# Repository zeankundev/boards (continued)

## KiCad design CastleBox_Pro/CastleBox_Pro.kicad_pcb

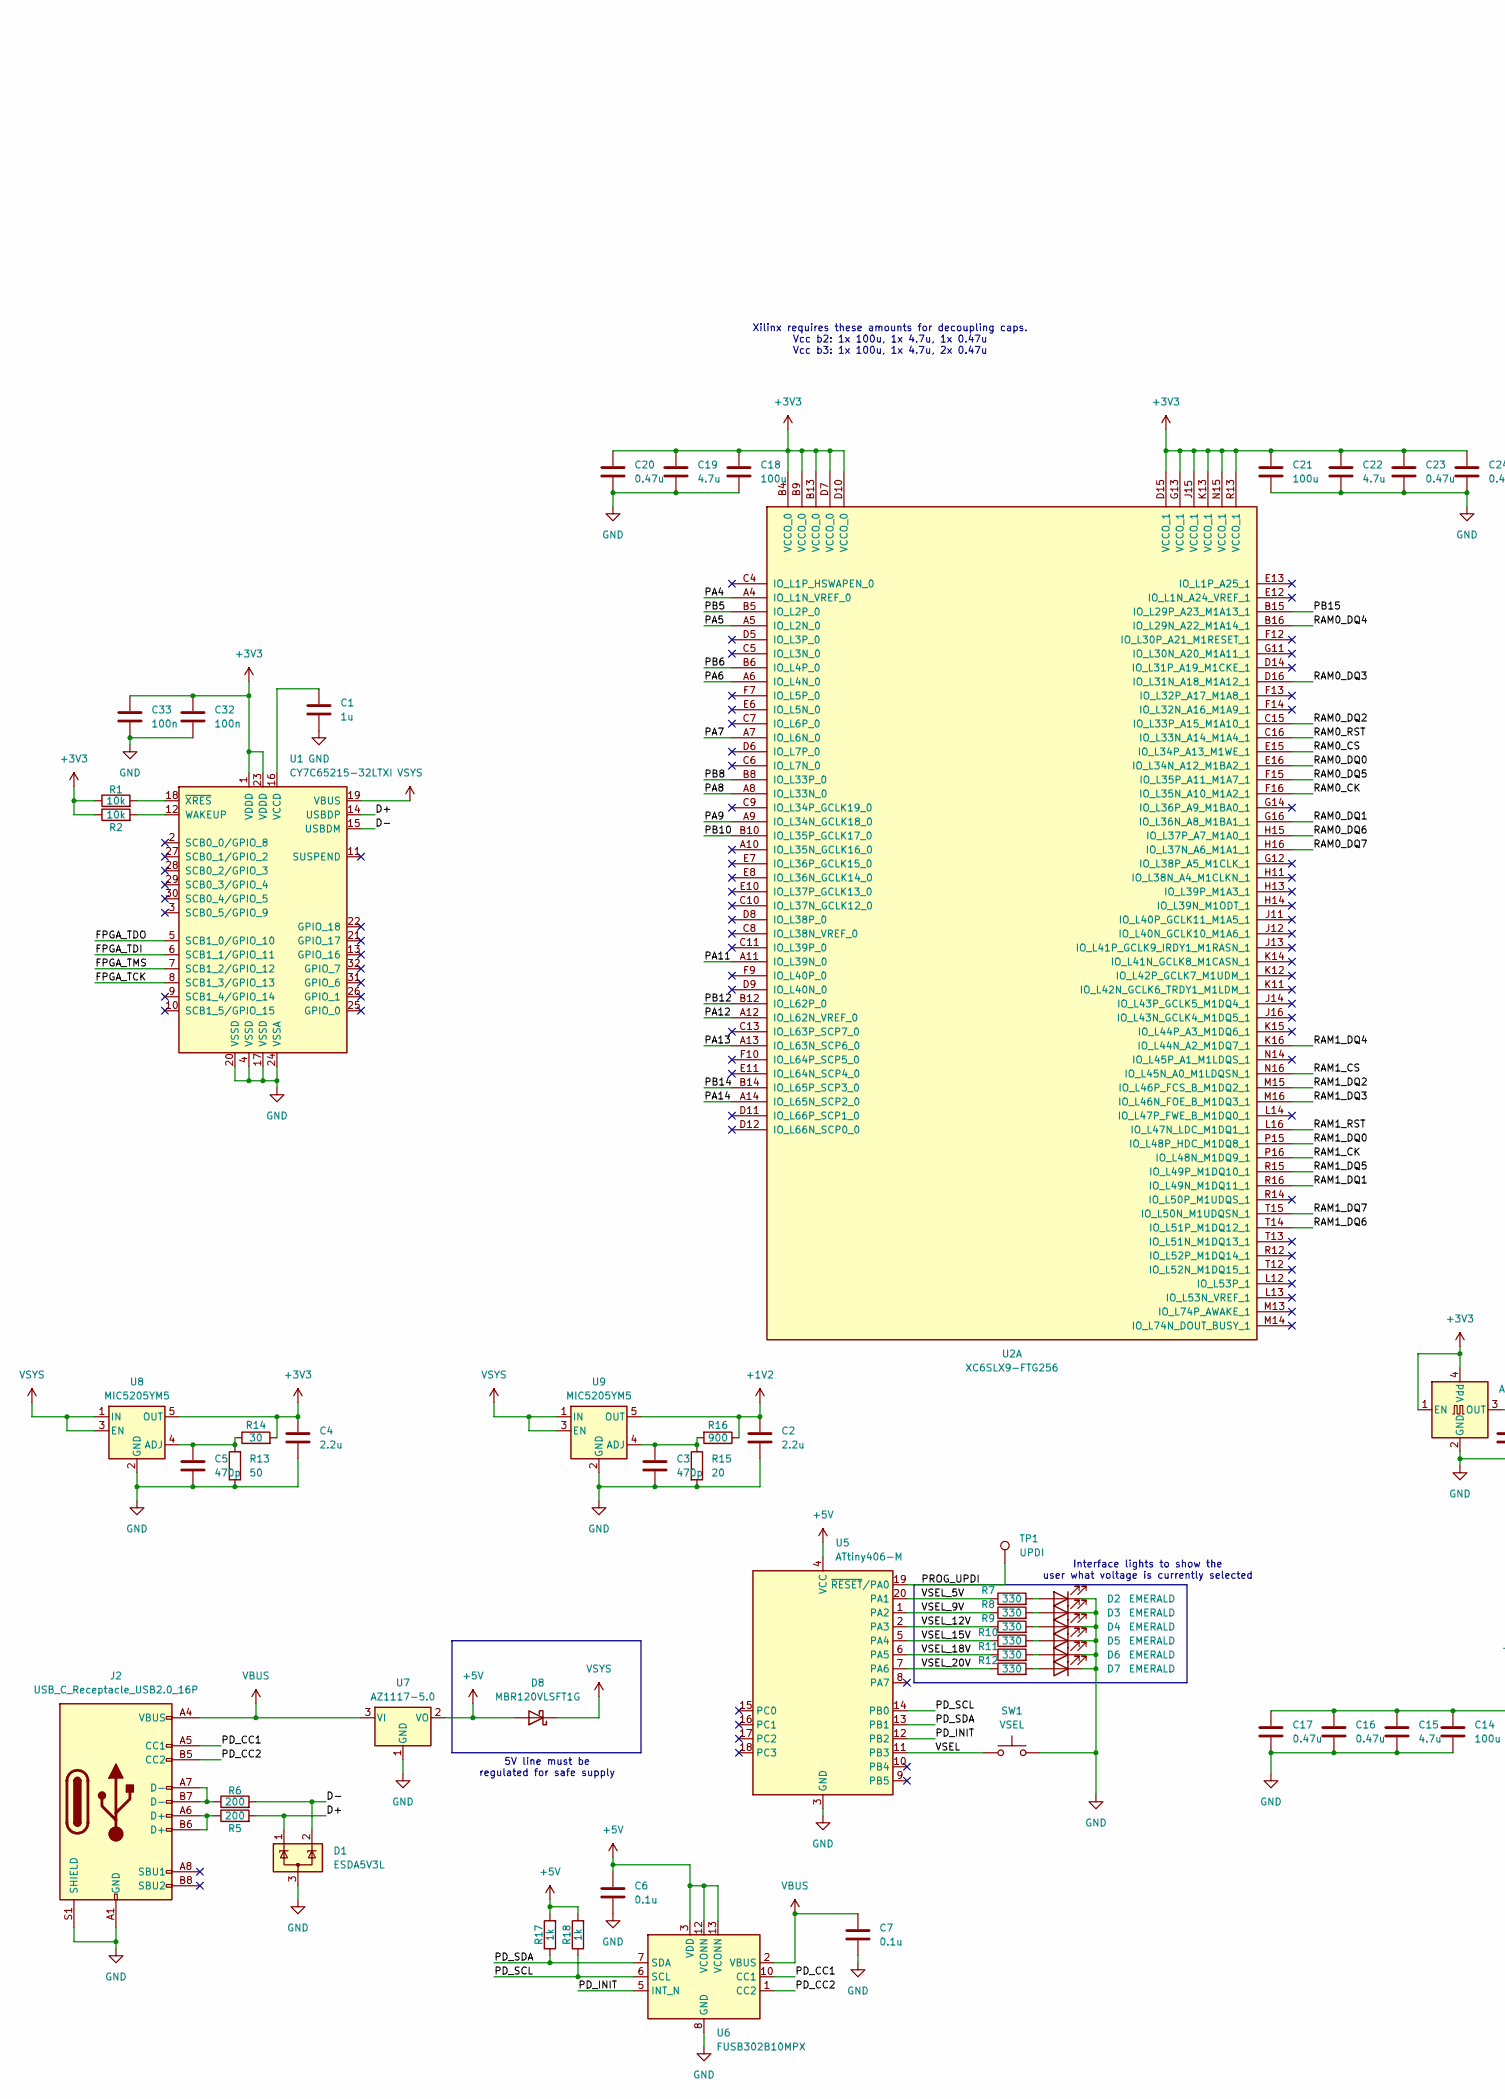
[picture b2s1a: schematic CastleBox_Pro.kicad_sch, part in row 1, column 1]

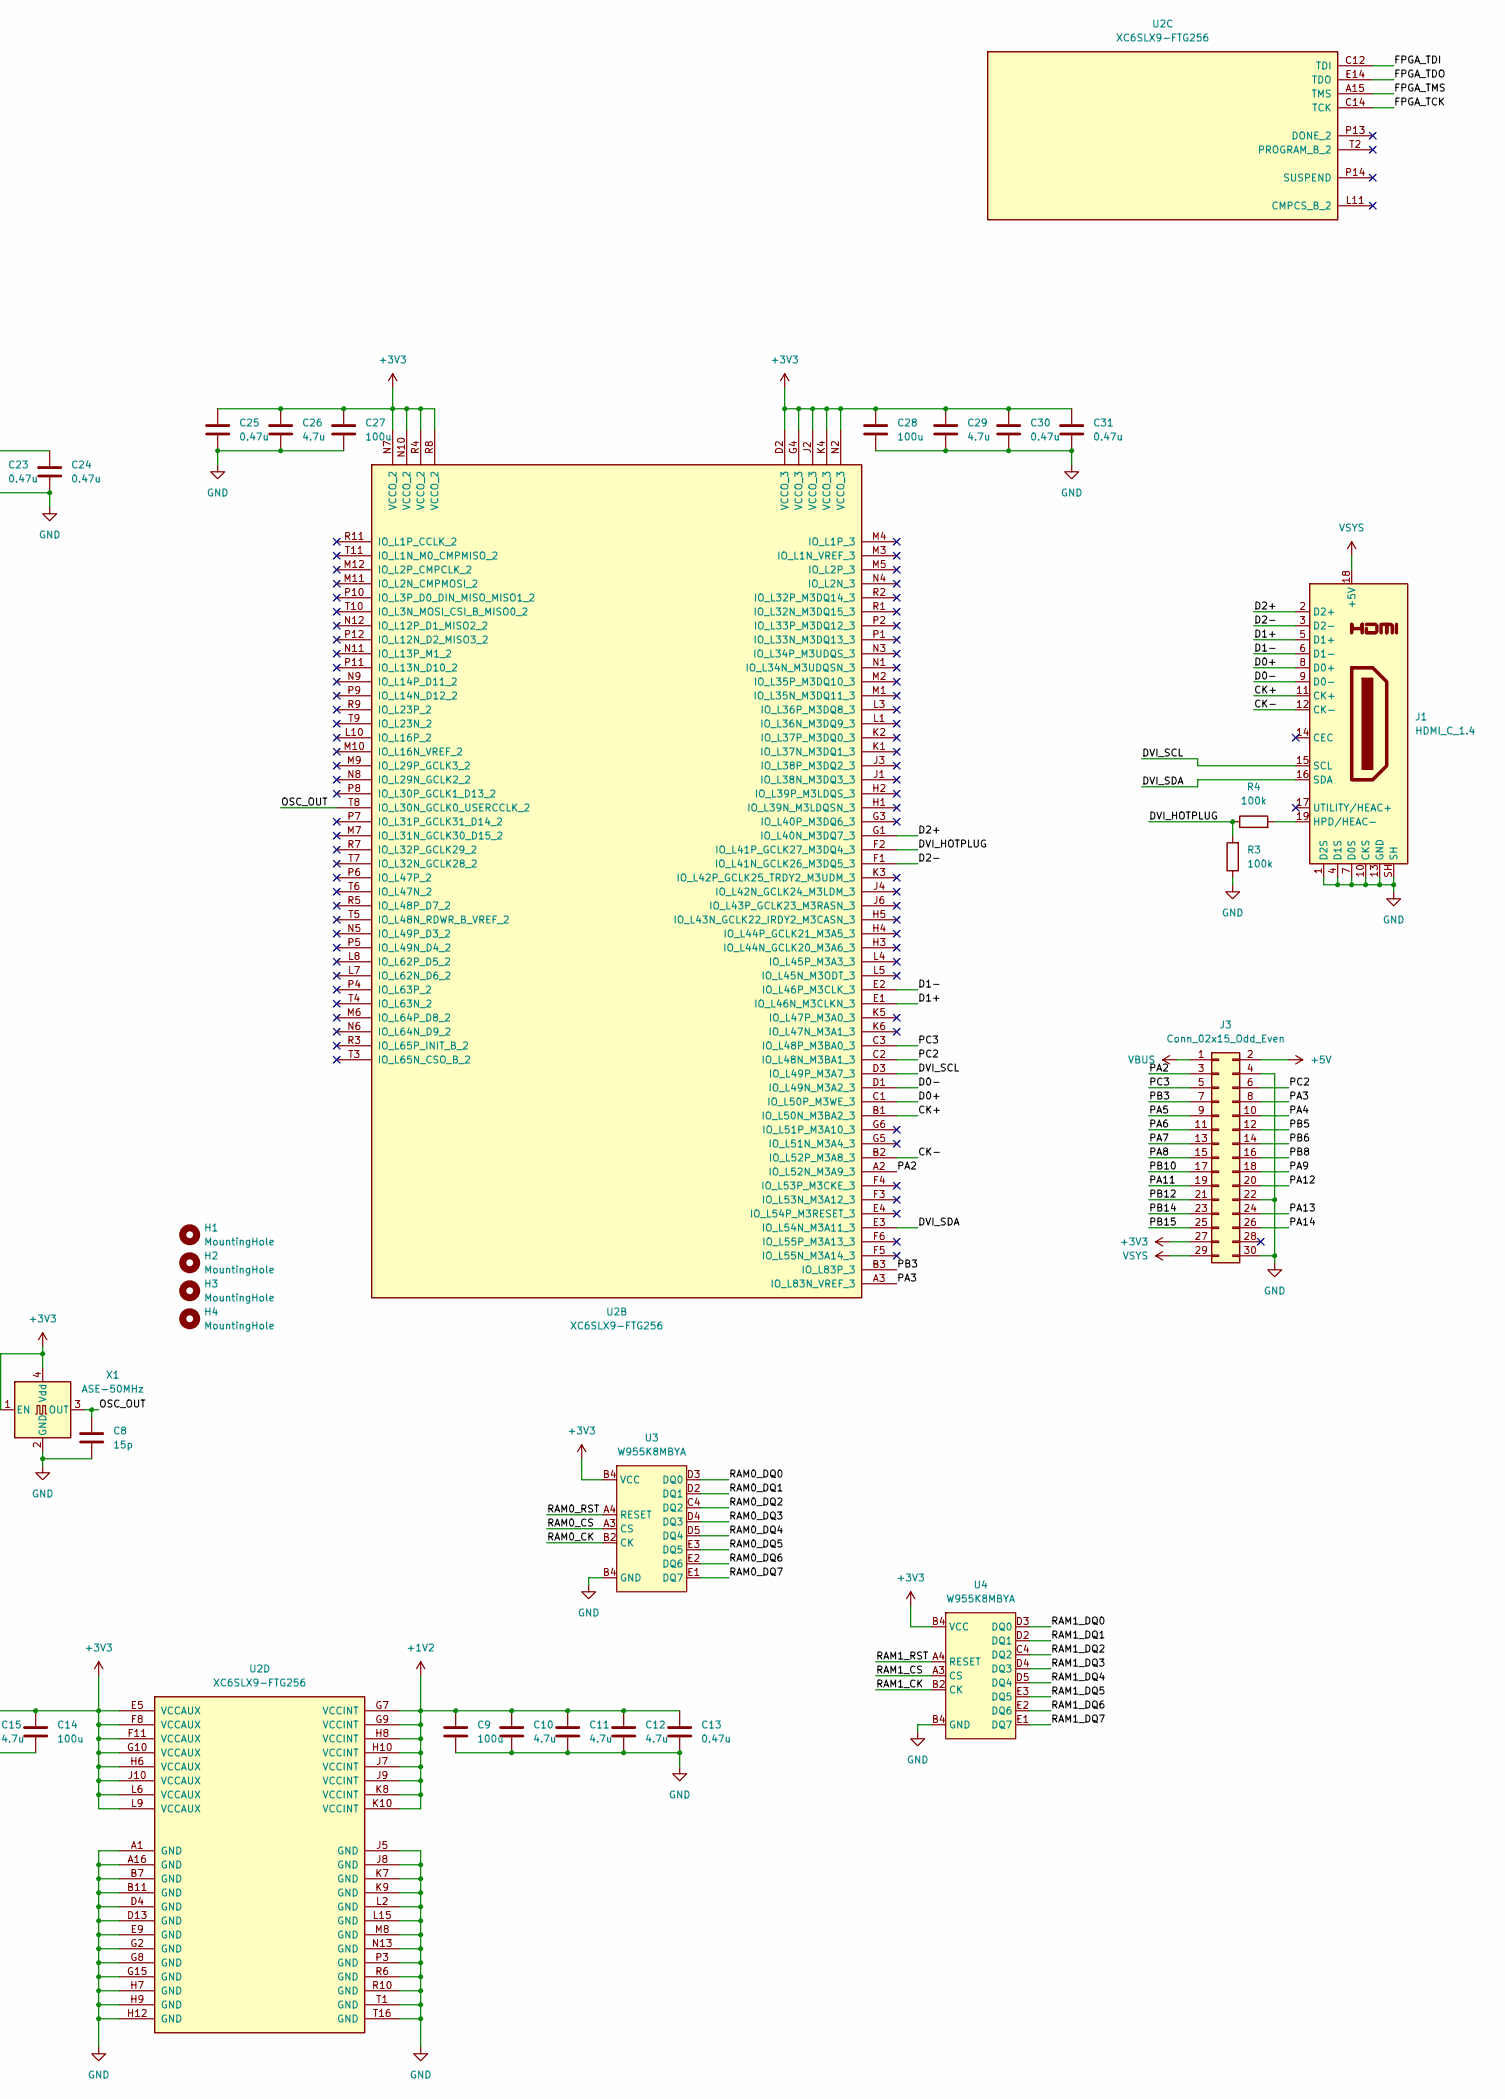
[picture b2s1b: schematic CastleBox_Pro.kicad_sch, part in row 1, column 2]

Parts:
C1: 1u; C_0402_1005Metric
C2, C4: 2.2u; C_0402_1005Metric
C3, C5: 470p; C_0402_1005Metric
C6, C7: 0.1u; C_0402_1005Metric
C8: 15p; C_0402_1005Metric
C9, C14, C18, C21, C27, C28: 100u; C_0402_1005Metric
C10, C11, C12, C15, C19, C22, C26, C29: 4.7u; C_0402_1005Metric
C13, C16, C17, C20, C23, C24, C25, C30, C31: 0.47u; C_0402_1005Metric
C32, C33: 100n; C_0402_1005Metric
D1: ESDA5V3L; SOT-23-3
D2, D3, D4, D5, D6, D7: EMERALD; LED_0402_1005Metric
D8: MBR120VLSFT1G; D_SOD-123F
H1, H2, H3, H4: MountingHole; MountingHole_2.1mm
J1: HDMI_C_1.4; VALCON_HD-RA-DSF12-TR
J2: USB_C_Receptacle_USB2.0_16P; USB_C_Receptacle_GCT_USB4105-xx-A_16P_TopMnt_Horizontal
J3: Conn_02x15_Odd_Even; PinHeader_2x15_P2.54mm_Vertical
R1, R2: 10k; R_0402_1005Metric
R3, R4: 100k; R_0402_1005Metric
R5, R6: 200; R_0402_1005Metric
R7, R8, R9, R10, R11, R12: 330; R_0402_1005Metric
R13: 50; R_0402_1005Metric
R14: 30; R_0402_1005Metric
R15: 20; R_0402_1005Metric
R16: 900; R_0402_1005Metric
R17, R18: 1k; R_0402_1005Metric
SW1: VSEL; SW_Push_1P1T_NO_Vertical_Wuerth_434133025816
TP1: UPDI; TestPoint_Pad_D1.0mm
U1: CY7C65215-32LTXI; QFN-32-1EP_5x5mm_P0.5mm_EP3.45x3.45mm
U2: XC6SLX9-FTG256; BGA-256_17.0x17.0mm_Layout16x16_P1.0mm_Ball0.5mm_Pad0.4mm_N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
U3, U4: W955K8MBYA
U5: ATtiny406-M; VQFN-20-1EP_3x3mm_P0.4mm_EP1.7x1.7mm
U6: FUSB302B10MPX; WQFN-14-1EP_2.5x2.5mm_P0.5mm_EP1.45x1.45mm
U7: AZ1117-5.0; SOT-89-3
U8, U9: MIC5205YM5; SOT-23-5
X1: ASE-50MHz; Oscillator_SMD_Abracon_ASE-4Pin_3.2x2.5mm

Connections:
+1V2: C2.1, C9.1, C10.1, C11.1, C12.1, C13.1, R16.1, U2.G7 (VCCINT), U2.G9 (VCCINT), U2.H8 (VCCINT), U2.H10 (VCCINT), U2.J7 (VCCINT), U2.J9 (VCCINT), U2.K8 (VCCINT), U2.K10 (VCCINT), U9.5 (OUT)
+5V: C6.1, D8.2 (A), J3.2, R17.2, R18.2, U5.4 (VCC), U6.3 (VDD), U6.4 (VDD), U6.12 (VCONN), U6.13 (VCONN), U7.2 (VO)
/CK+: J1.11 (CK+), U2.B1 (IO_L50N_M3BA2_3)
/CK-: J1.12 (CK-), U2.B2 (IO_L52P_M3A8_3)
/D0+: J1.8 (D0+), U2.C1 (IO_L50P_M3WE_3)
/D0-: J1.9 (D0-), U2.D1 (IO_L49N_M3A2_3)
/D1+: J1.5 (D1+), U2.E1 (IO_L46N_M3CLKN_3)
/D1-: J1.6 (D1-), U2.E2 (IO_L46P_M3CLK_3)
/D2+: J1.2 (D2+), U2.G1 (IO_L40N_M3DQ7_3)
/D2-: J1.3 (D2-), U2.F1 (IO_L41N_GCLK26_M3DQ5_3)
/D+: D1.1 (K), R5.2, U1.14 (USBDP)
/D-: D1.2 (K), R6.2, U1.15 (USBDM)
/DVI_HOTPLUG: R3.2, R4.1, U2.F2 (IO_L41P_GCLK27_M3DQ4_3)
/DVI_SCL: J1.15 (SCL), U2.D3 (IO_L49P_M3A7_3)
/DVI_SDA: J1.16 (SDA), U2.E3 (IO_L54N_M3A11_3)
/FPGA_TCK: U1.8 (SCB1_3/GPIO_13), U2.C14 (TCK)
/FPGA_TDI: U1.6 (SCB1_1/GPIO_11), U2.C12 (TDI)
/FPGA_TDO: U1.5 (SCB1_0/GPIO_10), U2.E14 (TDO)
/FPGA_TMS: U1.7 (SCB1_2/GPIO_12), U2.A15 (TMS)
/OSC_OUT: C8.1, U2.T8 (IO_L30N_GCLK0_USERCCLK_2), X1.3 (OUT)
/PA2: J3.3, U2.A2 (IO_L52N_M3A9_3)
/PA3: J3.8, U2.A3 (IO_L83N_VREF_3)
/PA4: J3.10, U2.A4 (IO_L1N_VREF_0)
/PA5: J3.9, U2.A5 (IO_L2N_0)
/PA6: J3.11, U2.A6 (IO_L4N_0)
/PA7: J3.13, U2.A7 (IO_L6N_0)
/PA8: J3.15, U2.A8 (IO_L33N_0)
/PA9: J3.18, U2.A9 (IO_L34N_GCLK18_0)
/PA11: J3.19, U2.A11 (IO_L39N_0)
/PA12: J3.20, U2.A12 (IO_L62N_VREF_0)
/PA13: J3.24, U2.A13 (IO_L63N_SCP6_0)
/PA14: J3.26, U2.A14 (IO_L65N_SCP2_0)
/PB3: J3.7, U2.B3 (IO_L83P_3)
/PB5: J3.12, U2.B5 (IO_L2P_0)
/PB6: J3.14, U2.B6 (IO_L4P_0)
/PB8: J3.16, U2.B8 (IO_L33P_0)
/PB10: J3.17, U2.B10 (IO_L35P_GCLK17_0)
/PB12: J3.21, U2.B12 (IO_L62P_0)
/PB14: J3.23, U2.B14 (IO_L65P_SCP3_0)
/PB15: J3.25, U2.B15 (IO_L29P_A23_M1A13_1)
/PC2: J3.6, U2.C2 (IO_L48N_M3BA1_3)
/PC3: J3.5, U2.C3 (IO_L48P_M3BA0_3)
/PD_CC1: J2.A5 (CC1), U6.10 (CC1), U6.11 (CC1)
/PD_CC2: J2.B5 (CC2), U6.1 (CC2), U6.14 (CC2)
/PD_INIT: U5.12 (PB2), U6.5 (INT_N)
/PD_SCL: R18.1, U5.14 (PB0), U6.6 (SCL)
/PD_SDA: R17.1, U5.13 (PB1), U6.7 (SDA)
/PROG_UPDI: TP1.1, U5.19 (~RESET/PA0)
/RAM0_CK: U2.F16 (IO_L35N_A10_M1A2_1), U3.B2 (CK)
/RAM0_CS: U2.E15 (IO_L34P_A13_M1WE_1), U3.A3 (CS)
/RAM0_DQ0: U2.E16 (IO_L34N_A12_M1BA2_1), U3.D3 (DQ0)
/RAM0_DQ1: U2.G16 (IO_L36N_A8_M1BA1_1), U3.D2 (DQ1)
/RAM0_DQ2: U2.C15 (IO_L33P_A15_M1A10_1), U3.C4 (DQ2)
/RAM0_DQ3: U2.D16 (IO_L31N_A18_M1A12_1), U3.D4 (DQ3)
/RAM0_DQ4: U2.B16 (IO_L29N_A22_M1A14_1), U3.D5 (DQ4)
/RAM0_DQ5: U2.F15 (IO_L35P_A11_M1A7_1), U3.E3 (DQ5)
/RAM0_DQ6: U2.H15 (IO_L37P_A7_M1A0_1), U3.E2 (DQ6)
/RAM0_DQ7: U2.H16 (IO_L37N_A6_M1A1_1), U3.E1 (DQ7)
/RAM0_RST: U2.C16 (IO_L33N_A14_M1A4_1), U3.A4 (RESET)
/RAM1_CK: U2.P16 (IO_L48N_M1DQ9_1), U4.B2 (CK)
/RAM1_CS: U2.N16 (IO_L45N_A0_M1LDQSN_1), U4.A3 (CS)
/RAM1_DQ0: U2.P15 (IO_L48P_HDC_M1DQ8_1), U4.D3 (DQ0)
/RAM1_DQ1: U2.R16 (IO_L49N_M1DQ11_1), U4.D2 (DQ1)
/RAM1_DQ2: U2.M15 (IO_L46P_FCS_B_M1DQ2_1), U4.C4 (DQ2)
/RAM1_DQ3: U2.M16 (IO_L46N_FOE_B_M1DQ3_1), U4.D4 (DQ3)
/RAM1_DQ4: U2.K16 (IO_L44N_A2_M1DQ7_1), U4.D5 (DQ4)
/RAM1_DQ5: U2.R15 (IO_L49P_M1DQ10_1), U4.E3 (DQ5)
/RAM1_DQ6: U2.T14 (IO_L51P_M1DQ12_1), U4.E2 (DQ6)
/RAM1_DQ7: U2.T15 (IO_L50N_M1UDQSN_1), U4.E1 (DQ7)
/RAM1_RST: U2.L16 (IO_L47N_LDC_M1DQ1_1), U4.A4 (RESET)
/VSEL: SW1.1, U5.11 (PB3)
/VSEL_5V: R7.1, U5.20 (PA1)
/VSEL_9V: R8.1, U5.1 (PA2)
/VSEL_12V: R9.1, U5.2 (PA3)
/VSEL_15V: R10.1, U5.5 (PA4)
/VSEL_18V: R11.1, U5.6 (PA5)
/VSEL_20V: R12.1, U5.7 (PA6)
unnamed: D2.2 (A), R7.2
unnamed: D3.2 (A), R8.2
unnamed: D4.2 (A), R9.2
unnamed: D5.2 (A), R10.2
unnamed: D6.2 (A), R11.2
unnamed: D7.2 (A), R12.2
unnamed: J1.19 (HPD/HEAC-), R4.2
unnamed: J2.A6 (D+), J2.B6 (D+), R5.1
unnamed: J2.A7 (D-), J2.B7 (D-), R6.1
unnamed: C1.1, U1.16 (VCCD)
unnamed: R2.2, U1.12 (WAKEUP)
unnamed: R1.2, U1.18 (~XRES)
unnamed: C5.1, R13.2, R14.1, U8.4 (ADJ)
unnamed: C3.1, R15.1, R16.2, U9.4 (ADJ)
VBUS: C7.1, J2.A4 (VBUS), J2.A9 (VBUS), J2.B4 (VBUS), J2.B9 (VBUS), J3.1, U6.2 (VBUS), U7.3 (VI)
VSYS: D8.1 (K), J1.18 (+5V), J3.29, U1.19 (VBUS), U8.1 (IN), U8.3 (EN), U9.1 (IN), U9.3 (EN)

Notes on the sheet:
5V line must be regulated for safe supply
Xilinx requires these amounts for decoupling caps. Vcc b2: 1x 100u, 1x 4.7u, 1x 0.47u Vcc b3: 1x 100u, 1x 4.7u, 2x 0.47u
Interface lights to show the user what voltage is currently selected

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
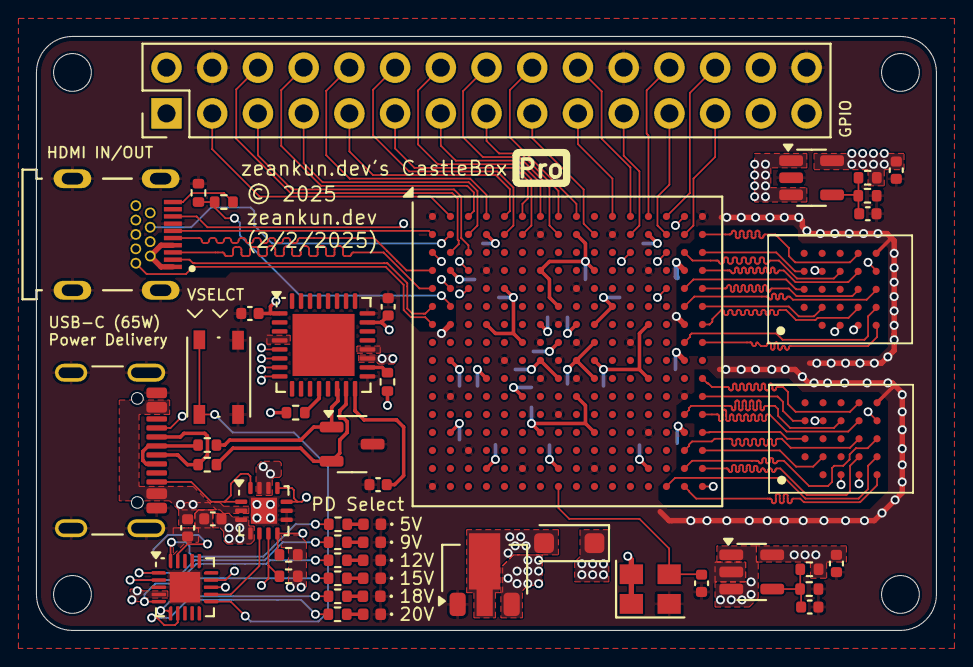
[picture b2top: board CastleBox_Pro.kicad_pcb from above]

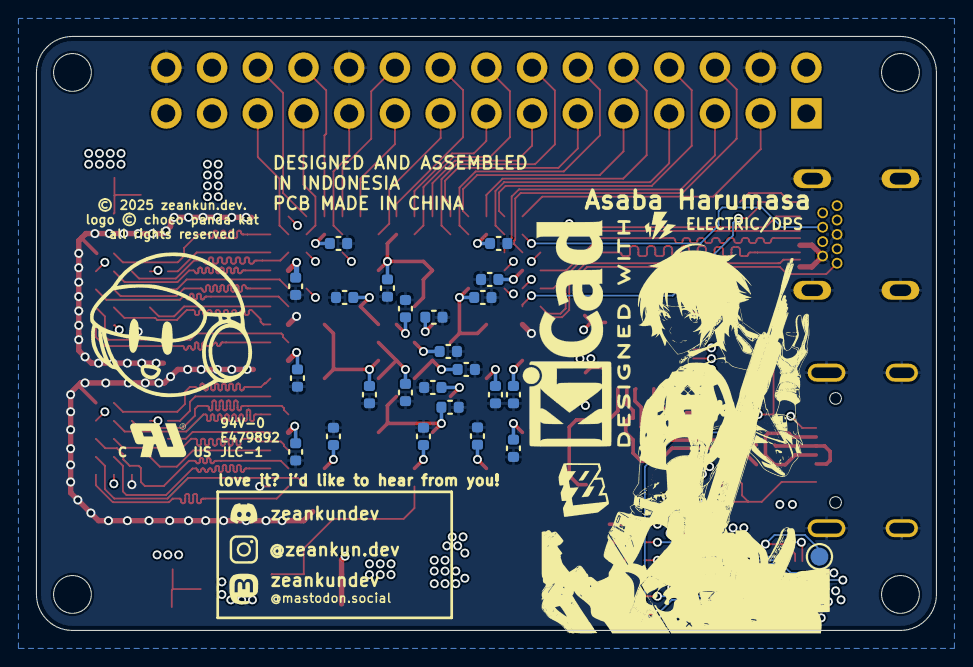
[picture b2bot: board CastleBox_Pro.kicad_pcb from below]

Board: 6 copper layers, 50.0 x 33.0 mm, 78 parts (24 on the bottom side), 95 nets.

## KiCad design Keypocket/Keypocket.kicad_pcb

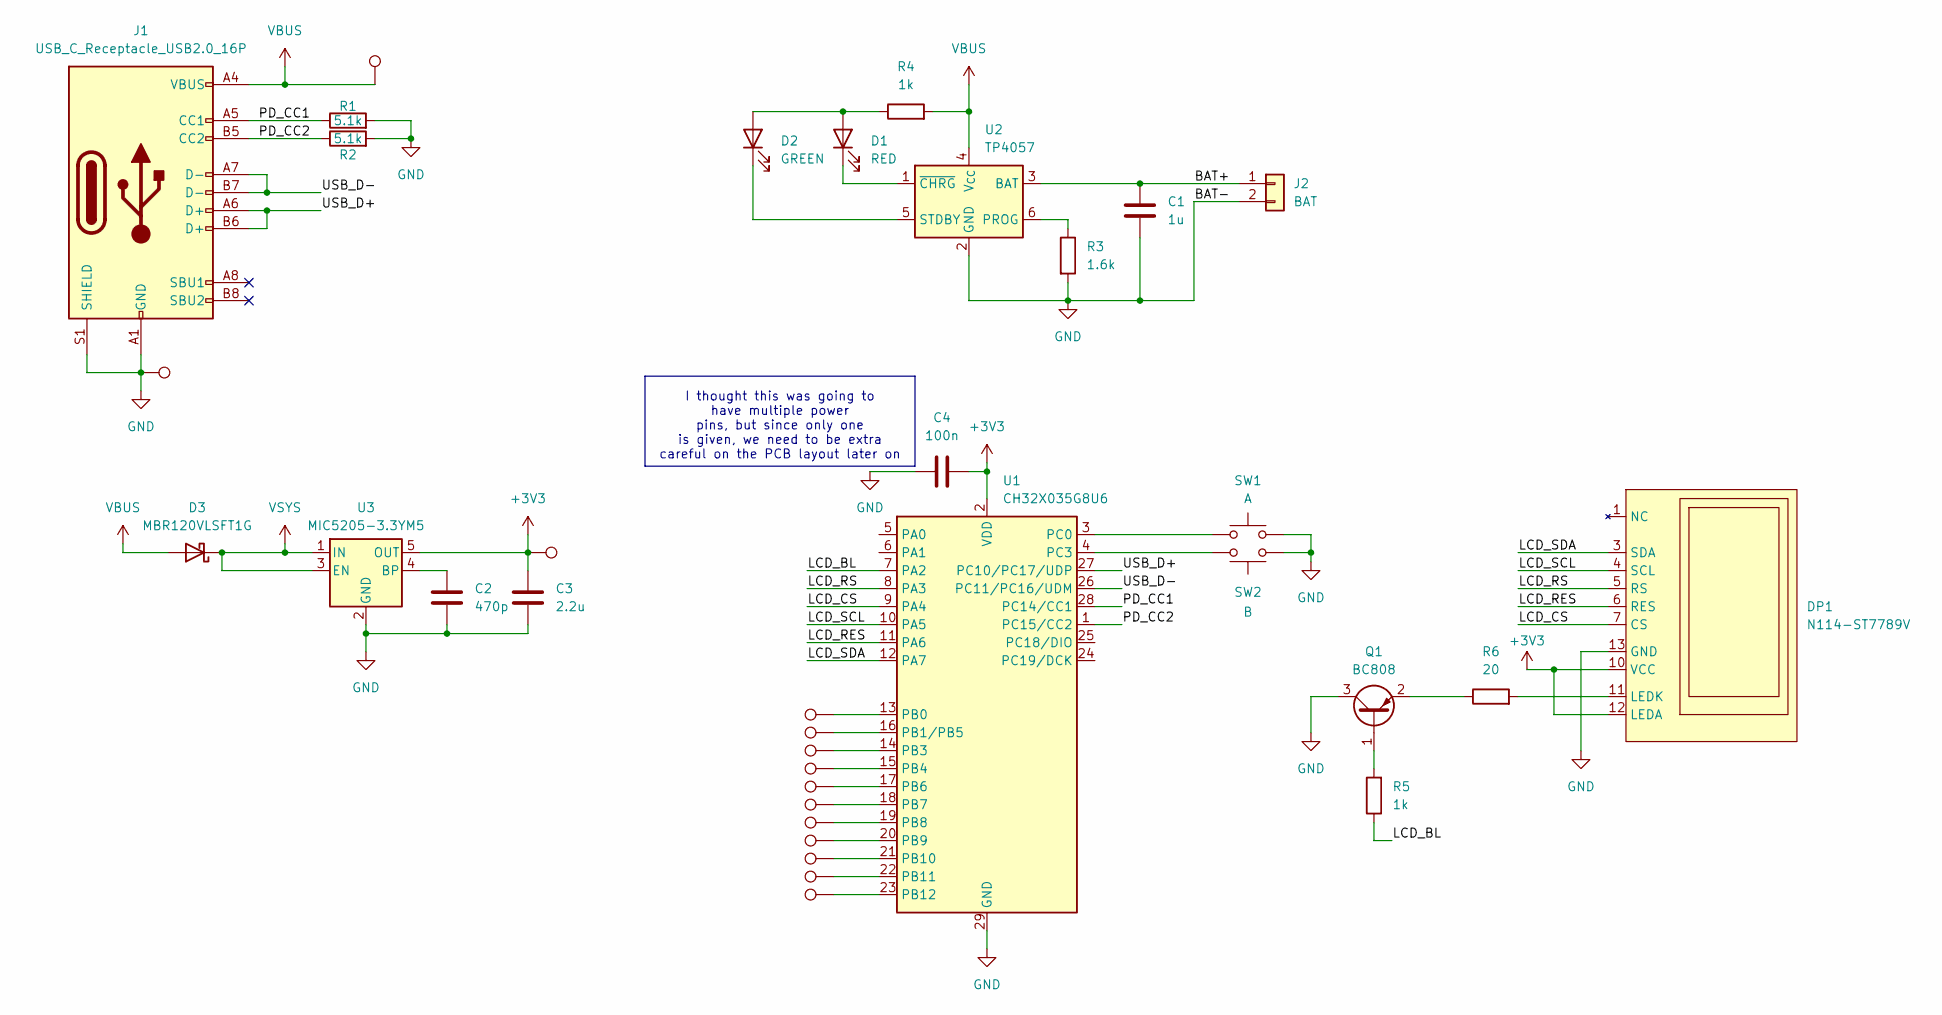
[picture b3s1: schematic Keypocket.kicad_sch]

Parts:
C1: 1u; C_0603_1608Metric
C2: 470p; C_0402_1005Metric
C3: 2.2u; C_0603_1608Metric
C4: 100n; C_0402_1005Metric
D1: RED; LED_0402_1005Metric
D2: GREEN; LED_0402_1005Metric
D3: MBR120VLSFT1G; D_SOD-123F
DP1: N114-ST7789V; ST7789-114
J1: USB_C_Receptacle_USB2.0_16P; USB_C_Receptacle_GCT_USB4110
J2: BAT; SolderWire-0.1sqmm_1x02_P3.6mm_D0.4mm_OD1mm
Q1: BC808; SOT-23
R1, R2: 5.1k; R_0402_1005Metric
R3: 1.6k; R_0402_1005Metric
R4, R5: 1k; R_0402_1005Metric
R6: 20; R_0402_1005Metric
SW1: A; SW_Push_1P1T_NO_Vertical_Wuerth_434133025816
SW2: B; SW_Push_1P1T_NO_Vertical_Wuerth_434133025816
TP1, TP2, TP3, TP4, TP5, TP6, TP7, TP8, TP9, TP10, TP11: TestPoint; TestPoint_Keystone_5015_Micro_Mini
TP12, TP13, TP14: TestPoint; TestPoint_Pad_2.0x2.0mm
U1: CH32X035G8U6; QFN-28-1EP_4x4mm_P0.4mm_EP2.7x2.7mm
U2: TP4057; TSOT-23-6
U3: MIC5205-3.3YM5; SOT-23-5

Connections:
+3V3: C3.1, C4.2, DP1.10 (VCC), DP1.12 (LEDA), TP12.1, U1.2 (VDD), U3.5 (OUT)
/BAT+: C1.1, J2.1, U2.3 (BAT)
/LCD_BL: R5.1, U1.7 (PA2)
/LCD_CS: DP1.7 (CS), U1.9 (PA4)
/LCD_RES: DP1.6 (RES), U1.11 (PA6)
/LCD_RS: DP1.5 (RS), U1.8 (PA3)
/LCD_SCL: DP1.4 (SCL), U1.10 (PA5)
/LCD_SDA: DP1.3 (SDA), U1.12 (PA7)
/PD_CC1: J1.A5 (CC1), R1.1, U1.28 (PC14/CC1)
/PD_CC2: J1.B5 (CC2), R2.1, U1.1 (PC15/CC2)
/USB_D+: J1.A6 (D+), J1.B6 (D+), U1.27 (PC10/PC17/UDP)
/USB_D-: J1.A7 (D-), J1.B7 (D-), U1.26 (PC11/PC16/UDM)
GND: C1.2, C2.2, C3.2, C4.1, DP1.8 (GND), DP1.13 (GND), J1.A1 (GND), J1.A12 (GND), J1.B1 (GND), J1.B12 (GND), J1.S1 (SHIELD), J2.2, Q1.3 (C), R1.2, R2.2, R3.2, SW1.2, SW2.1, TP14.1, U1.29 (GND), U2.2 (GND), U3.2 (GND)
unnamed: D1.2 (A), D2.2 (A), R4.1
unnamed: D1.1 (K), U2.1 (~CHRG)
unnamed: D2.1 (K), U2.5 (STDBY)
unnamed: DP1.11 (LEDK), R6.2
unnamed: Q1.1 (B), R5.2
unnamed: Q1.2 (E), R6.1
unnamed: TP1.1, U1.13 (PB0)
unnamed: TP2.1, U1.16 (PB1/PB5)
unnamed: TP3.1, U1.14 (PB3)
unnamed: TP4.1, U1.15 (PB4)
unnamed: TP5.1, U1.17 (PB6)
unnamed: TP6.1, U1.18 (PB7)
unnamed: TP7.1, U1.19 (PB8)
unnamed: TP8.1, U1.20 (PB9)
unnamed: TP9.1, U1.21 (PB10)
unnamed: TP10.1, U1.22 (PB11)
unnamed: TP11.1, U1.23 (PB12)
unnamed: SW1.1, U1.3 (PC0)
unnamed: SW2.2, U1.4 (PC3)
unnamed: R3.1, U2.6 (PROG)
unnamed: C2.1, U3.4 (BP)
VBUS: D3.2 (A), J1.A4 (VBUS), J1.A9 (VBUS), J1.B4 (VBUS), J1.B9 (VBUS), R4.2, TP13.1, U2.4 (V_{CC})
VSYS: D3.1 (K), U3.1 (IN), U3.3 (EN)

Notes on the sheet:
I thought this was going to have multiple power pins, but since only one is given, we need to be extra careful on the PCB layout later on

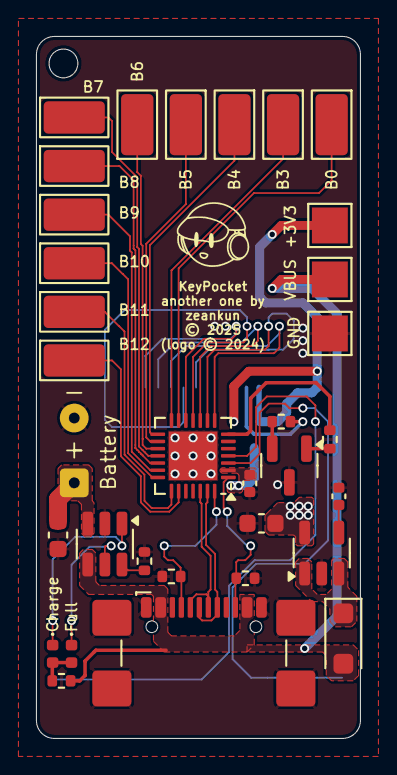
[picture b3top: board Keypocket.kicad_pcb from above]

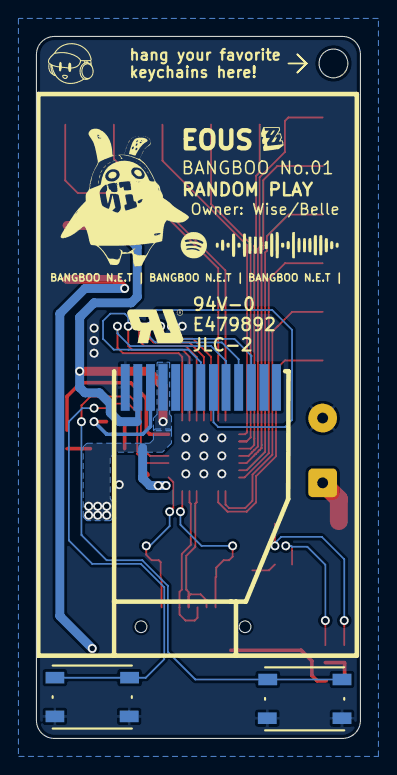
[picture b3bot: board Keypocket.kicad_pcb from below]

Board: 2 copper layers, 18.0 x 39.0 mm, 36 parts (3 on the bottom side), 36 nets.

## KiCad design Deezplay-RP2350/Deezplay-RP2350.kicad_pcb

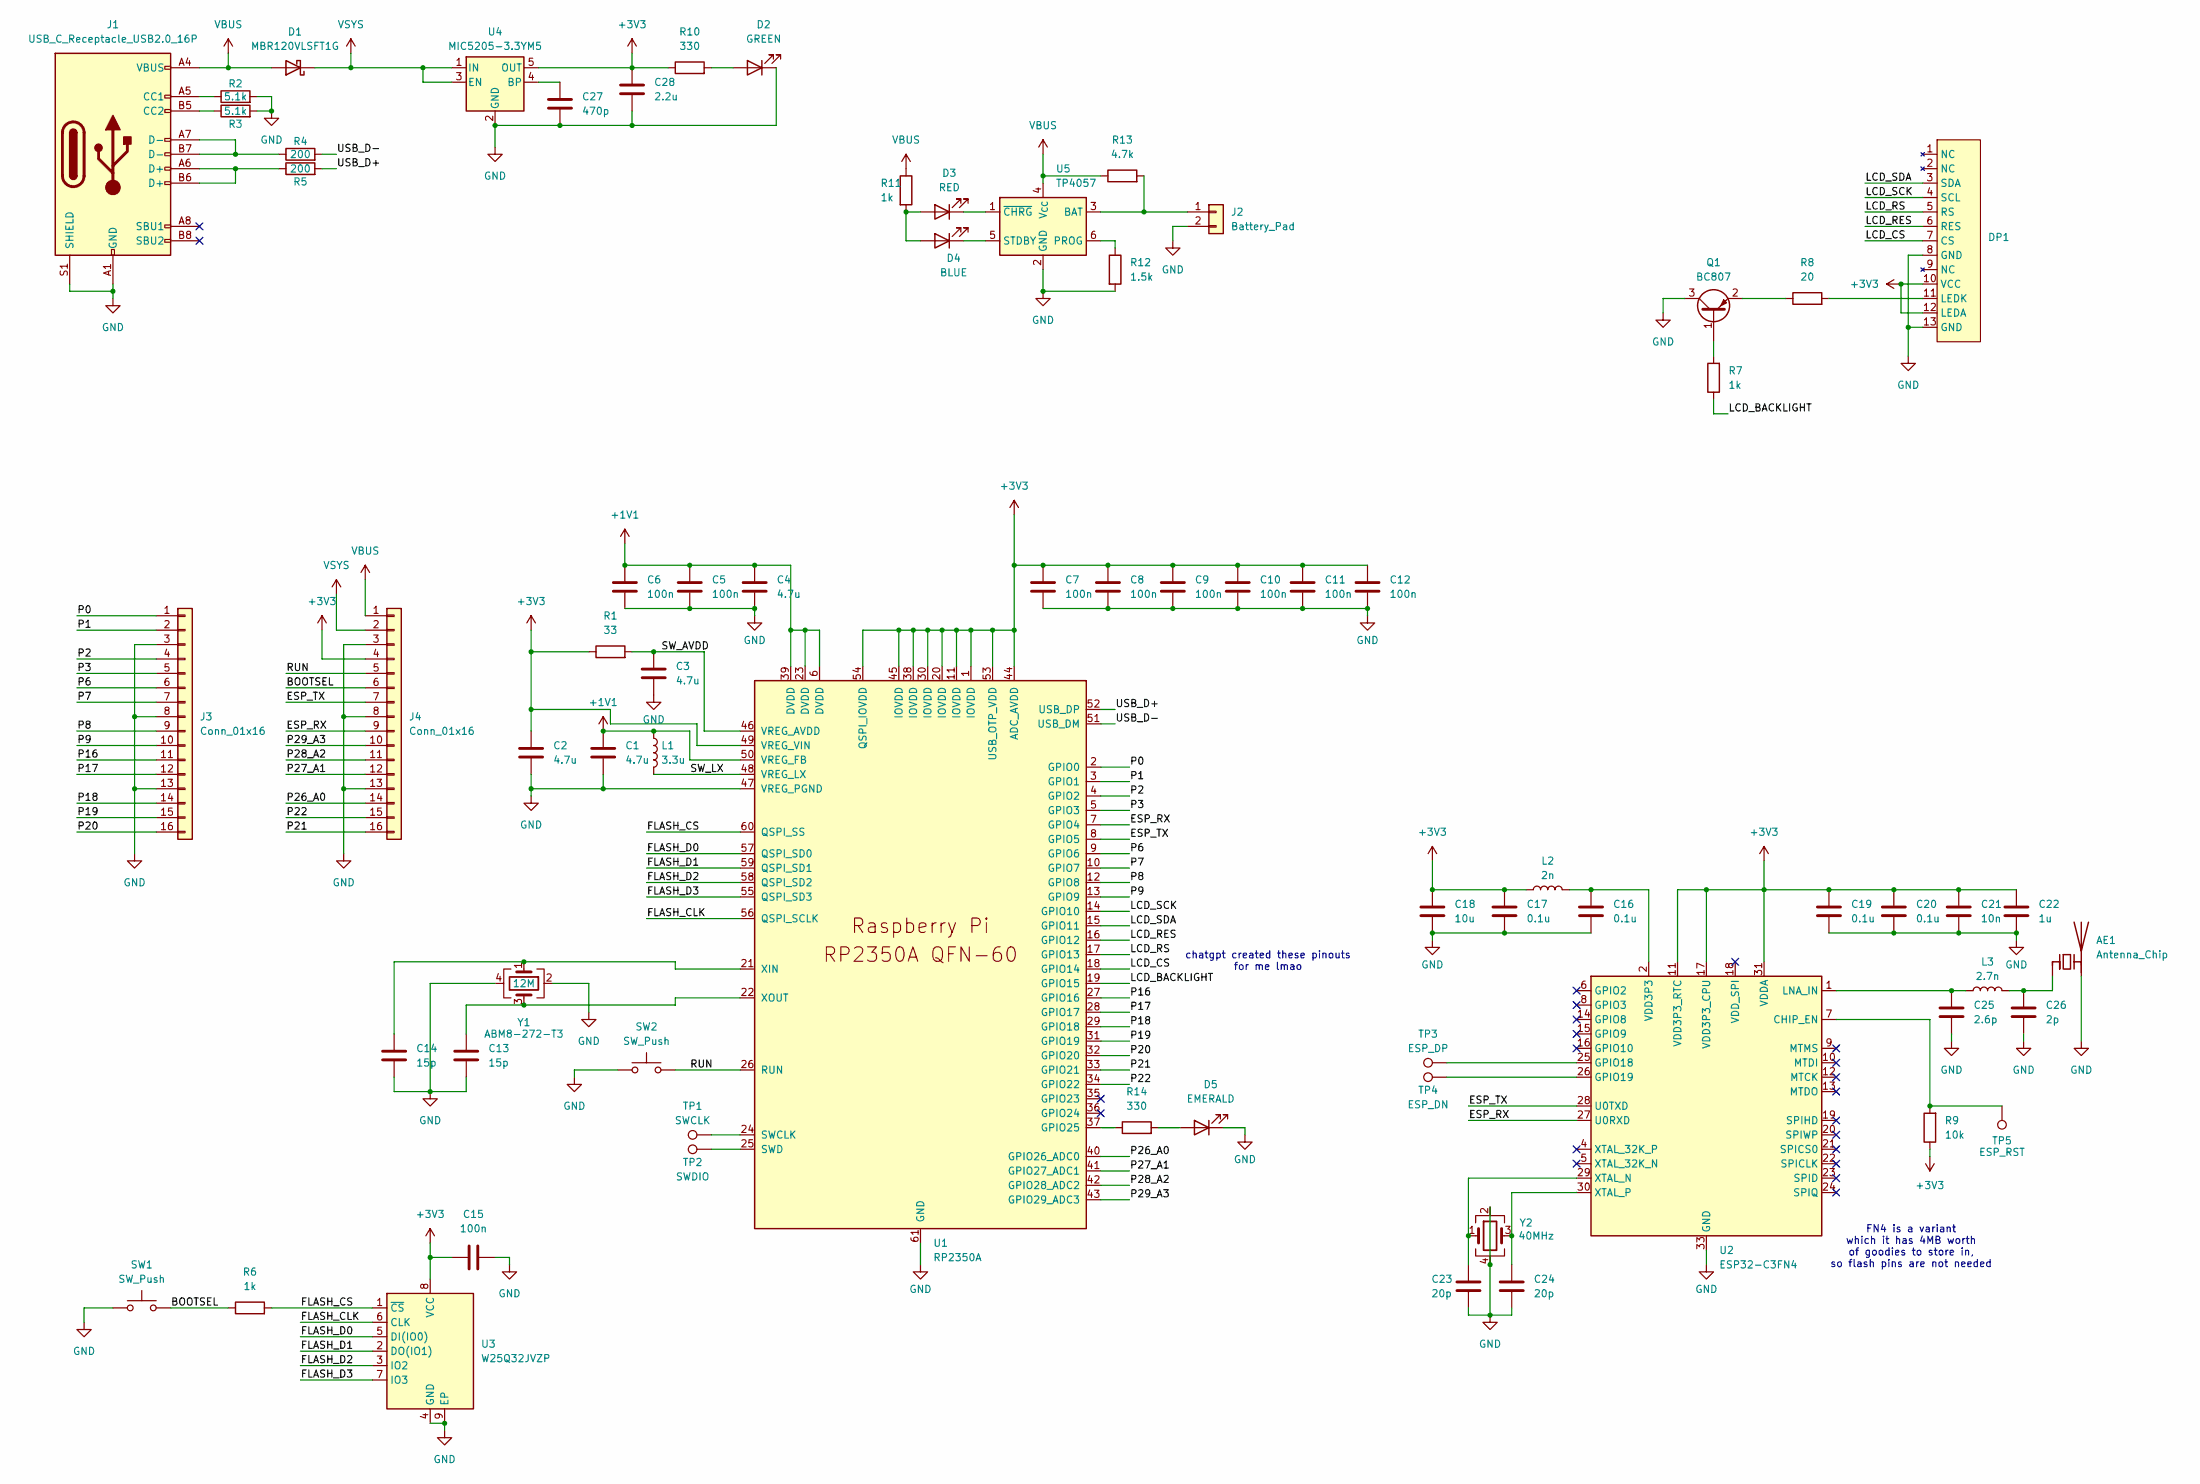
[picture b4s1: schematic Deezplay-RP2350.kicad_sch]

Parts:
AE1: Antenna_Chip; Texas_SWRA117D_2.4GHz_Left
C1, C2, C3, C4: 4.7u; C_0402_1005Metric
C5, C6, C7, C8, C9, C10, C11, C12, C15: 100n; C_0402_1005Metric
C13, C14: 15p; C_0402_1005Metric
C16, C17, C19, C20: 0.1u; C_0402_1005Metric
C18: 10u; C_0402_1005Metric
C21: 10n; C_0402_1005Metric
C22: 1u; C_0402_1005Metric
C23, C24: 20p; C_0402_1005Metric
C25: 2.6p; C_0402_1005Metric
C26: 2p; C_0402_1005Metric
C27: 470p; C_0402_1005Metric
C28: 2.2u; C_0402_1005Metric
D1: MBR120VLSFT1G; D_SOD-123F
D2: GREEN; LED_0402_1005Metric
D3: RED; LED_0402_1005Metric
D4: BLUE; LED_0402_1005Metric
D5: EMERALD; LED_0402_1005Metric
DP1: N114-2413THBIG01-H13
J1: USB_C_Receptacle_USB2.0_16P; USB_C_Receptacle_GCT_USB4105-xx-A_16P_TopMnt_Horizontal
J2: Battery_Pad; JST_PH_B2B-PH-SM4-TB_1x02-1MP_P2.00mm_Vertical
J3, J4: Conn_01x16; PinHeader_1x16_P2.54mm_Vertical
L1: 3.3u; L_Murata_DFE201610P
L2: 2n; L_0402_1005Metric
L3: 2.7n; L_0402_1005Metric
Q1: BC807; SOT-23
R1: 33; R_0402_1005Metric
R2, R3: 5.1k; R_0402_1005Metric
R4, R5: 200; R_0402_1005Metric
R6, R7, R11: 1k; R_0402_1005Metric
R8: 20; R_0402_1005Metric
R9: 10k; R_0402_1005Metric
R10, R14: 330; R_0402_1005Metric
R12: 1.5k; R_0402_1005Metric
R13: 4.7k; R_0402_1005Metric
SW1, SW2: SW_Push; SW_Push_1P1T_NO_Vertical_Wuerth_434133025816
TP1: SWCLK; TestPoint_Pad_D1.0mm
TP2: SWDIO; TestPoint_Pad_D1.0mm
TP3: ESP_DP; TestPoint_Pad_D1.0mm
TP4: ESP_DN; TestPoint_Pad_D1.0mm
TP5: ESP_RST; TestPoint_Pad_D1.0mm
U1: RP2350A; RP2350-QFN-60-1EP_7x7_P0.4mm_EP3.4x3.4mm_ThermalVias
U2: ESP32-C3FN4; QFN-32-1EP_5x5mm_P0.5mm_EP3.7x3.7mm
U3: W25Q32JVZP; Winbond_USON-8-1EP_3x2mm_P0.5mm_EP0.2x1.6mm
U4: MIC5205-3.3YM5; SOT-23-5
U5: TP4057; TSOT-23-6
Y1: 12M; Crystal_SMD_3225-4Pin_3.2x2.5mm
Y2: 40MHz; Crystal_SMD_2016-4Pin_2.0x1.6mm

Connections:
+1V1: C1.1, C4.1, C5.1, C6.1, L1.1, U1.6 (DVDD), U1.23 (DVDD), U1.39 (DVDD), U1.50 (VREG_FB)
+3V3: C2.1, C7.1, C8.1, C9.1, C10.1, C11.1, C12.1, C15.1, C17.1, C18.1, C19.1, C20.1, C21.1, C22.1, C28.1, DP1.10 (VCC), DP1.12 (LEDA), J4.4, L2.1, R1.1, R9.1, R10.1, U1.1 (IOVDD), U1.11 (IOVDD), U1.20 (IOVDD), U1.30 (IOVDD), U1.38 (IOVDD), U1.44 (ADC_AVDD), U1.45 (IOVDD), U1.49 (VREG_VIN), U1.53 (USB_OTP_VDD), U1.54 (QSPI_IOVDD), U2.11 (VDD3P3_RTC), U2.17 (VDD3P3_CPU), U2.31 (VDDA), U2.32 (VDDA), U3.8 (VCC), U4.5 (OUT)
/BOOTSEL: J4.6, R6.1, SW1.2
/ESP_RX: J4.9, U1.7 (GPIO4), U2.27 (U0RXD)
/ESP_TX: J4.7, U1.8 (GPIO5), U2.28 (U0TXD)
/FLASH_CLK: U1.56 (QSPI_SCLK), U3.6 (CLK)
/FLASH_CS: R6.2, U1.60 (QSPI_SS), U3.1 (~CS)
/FLASH_D0: U1.57 (QSPI_SD0), U3.5 (DI(IO0))
/FLASH_D1: U1.59 (QSPI_SD1), U3.2 (DO(IO1))
/FLASH_D2: U1.58 (QSPI_SD2), U3.3 (IO2)
/FLASH_D3: U1.55 (QSPI_SD3), U3.7 (IO3)
/LCD_BACKLIGHT: R7.1, U1.19 (GPIO15)
/LCD_CS: DP1.7 (CS), U1.18 (GPIO14)
/LCD_RES: DP1.6 (RES), U1.16 (GPIO12)
/LCD_RS: DP1.5 (RS), U1.17 (GPIO13)
/LCD_SCK: DP1.4 (SCL), U1.14 (GPIO10)
/LCD_SDA: DP1.3 (SDA), U1.15 (GPIO11)
/P0: J3.1, U1.2 (GPIO0)
/P1: J3.2, U1.3 (GPIO1)
/P2: J3.4, U1.4 (GPIO2)
/P3: J3.5, U1.5 (GPIO3)
/P6: J3.6, U1.9 (GPIO6)
/P7: J3.7, U1.10 (GPIO7)
/P8: J3.9, U1.12 (GPIO8)
/P9: J3.10, U1.13 (GPIO9)
/P16: J3.11, U1.27 (GPIO16)
/P17: J3.12, U1.28 (GPIO17)
/P18: J3.14, U1.29 (GPIO18)
/P19: J3.15, U1.31 (GPIO19)
/P20: J3.16, U1.32 (GPIO20)
/P21: J4.16, U1.33 (GPIO21)
/P22: J4.15, U1.34 (GPIO22)
/P26_A0: J4.14, U1.40 (GPIO26_ADC0)
/P27_A1: J4.12, U1.41 (GPIO27_ADC1)
/P28_A2: J4.11, U1.42 (GPIO28_ADC2)
/P29_A3: J4.10, U1.43 (GPIO29_ADC3)
/RUN: J4.5, SW2.2, U1.26 (RUN)
/SW_AVDD: C3.1, R1.2, U1.46 (VREG_AVDD)
/SW_LX: L1.2, U1.48 (VREG_LX)
/USB_D+: R5.2, U1.52 (USB_DP)
/USB_D-: R4.2, U1.51 (USB_DM)
GND: AE1.2 (PCB_Trace), C1.2, C2.2, C3.2, C4.2, C5.2, C6.2, C7.2, C8.2, C9.2, C10.2, C11.2, C12.2, C13.2, C14.2, C15.2, C16.2, C17.2, C18.2, C19.2, C20.2, C21.2, C22.2, C23.2, C24.2, C25.2, C26.2, C27.2, C28.2, D2.1 (K), D5.1 (K), DP1.8 (GND), DP1.13 (GND), J1.A1 (GND), J1.A12 (GND), J1.B1 (GND), J1.B12 (GND), J1.S1 (SHIELD), J2.2, J3.3, J3.8, J3.13, J4.3, J4.8, J4.13, Q1.3 (C), R2.2, R3.2, R12.2, SW1.1, SW2.1, U1.47 (VREG_PGND), U1.61 (GND), U2.33 (GND), U3.4 (GND), U3.9 (EP), U4.2 (GND), U5.2 (GND), Y1.2, Y1.4, Y2.2, Y2.4
unnamed: AE1.1 (FEED), C26.1, L3.2
unnamed: C16.1, L2.2, U2.2 (VDD3P3), U2.3 (VDD3P3)
unnamed: D2.2 (A), R10.2
unnamed: D3.2 (A), D4.2 (A), R11.2
unnamed: D3.1 (K), U5.1 (~CHRG)
unnamed: D4.1 (K), U5.5 (STDBY)
unnamed: D5.2 (A), R14.2
unnamed: DP1.11 (LEDK), R8.2
unnamed: J1.A5 (CC1), R2.1
unnamed: J1.B5 (CC2), R3.1
unnamed: J1.A6 (D+), J1.B6 (D+), R5.1
unnamed: J1.A7 (D-), J1.B7 (D-), R4.1
unnamed: J2.1, R13.2, U5.3 (BAT)
unnamed: Q1.1 (B), R7.2
unnamed: Q1.2 (E), R8.1
unnamed: R14.1, U1.37 (GPIO25)
unnamed: TP1.1, U1.24 (SWCLK)
unnamed: TP2.1, U1.25 (SWD)
unnamed: C14.1, U1.21 (XIN), Y1.1
unnamed: C13.1, U1.22 (XOUT), Y1.3
unnamed: R9.2, TP5.1, U2.7 (CHIP_EN)
unnamed: TP3.1, U2.25 (GPIO18)
unnamed: TP4.1, U2.26 (GPIO19)
unnamed: C25.1, L3.1, U2.1 (LNA_IN)
unnamed: C23.1, U2.29 (XTAL_N), Y2.1
unnamed: C24.1, U2.30 (XTAL_P), Y2.3
unnamed: C27.1, U4.4 (BP)
unnamed: R12.1, U5.6 (PROG)
VBUS: D1.2 (A), J1.A4 (VBUS), J1.A9 (VBUS), J1.B4 (VBUS), J1.B9 (VBUS), J4.1, R11.1, R13.1, U5.4 (V_{CC})
VSYS: D1.1 (K), J4.2, U4.1 (IN), U4.3 (EN)

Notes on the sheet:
FN4 is a variant which it has 4MB worth of goodies to store in, so flash pins are not needed
chatgpt created these pinouts for me lmao
